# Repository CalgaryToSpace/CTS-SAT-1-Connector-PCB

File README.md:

# CTS-SAT-1-Connector-PCB
A PCB with SMD connector receptacles to find pin 1 more easily

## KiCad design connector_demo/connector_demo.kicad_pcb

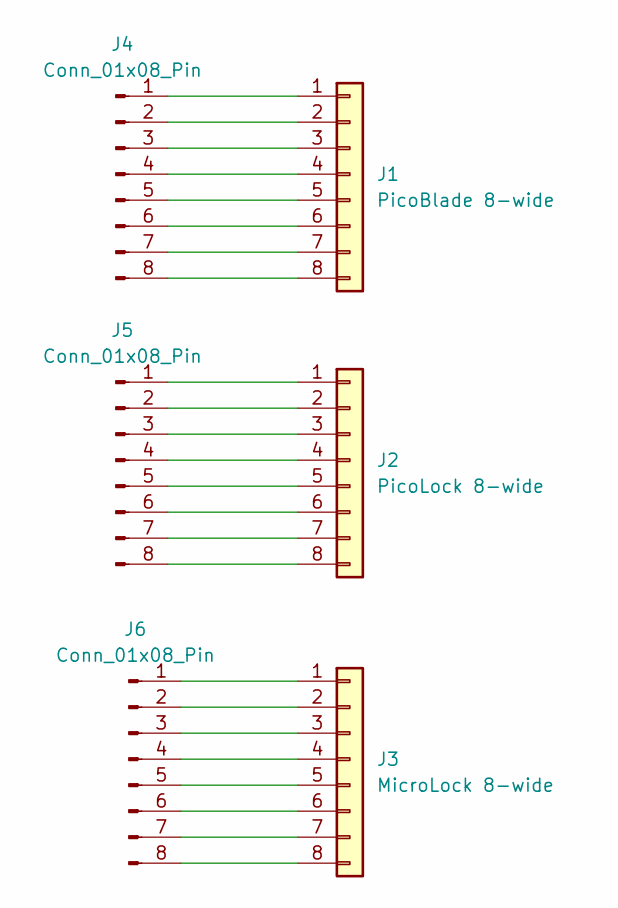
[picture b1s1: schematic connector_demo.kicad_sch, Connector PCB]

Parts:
J1: PicoBlade 8-wide; Molex_PicoBlade_53261-0871_1x08-1MP_P1.25mm_Horizontal
J2: PicoLock 8-wide; Molex_Pico-Lock_504050-0891_1x08-1MP_P1.50mm_Horizontal
J3: MicroLock 8-wide; CONN08_5055670871_MOL
J4, J5, J6: Conn_01x08_Pin; PinHeader_1x08_P2.54mm_Vertical

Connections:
unnamed: J1.1, J4.1
unnamed: J1.2, J4.2
unnamed: J1.3, J4.3
unnamed: J1.4, J4.4
unnamed: J1.5, J4.5
unnamed: J1.6, J4.6
unnamed: J1.7, J4.7
unnamed: J1.8, J4.8
unnamed: J2.1, J5.1
unnamed: J2.2, J5.2
unnamed: J2.3, J5.3
unnamed: J2.4, J5.4
unnamed: J2.5, J5.5
unnamed: J2.6, J5.6
unnamed: J2.7, J5.7
unnamed: J2.8, J5.8
unnamed: J3.1, J6.1
unnamed: J3.2, J6.2
unnamed: J3.3, J6.3
unnamed: J3.4, J6.4
unnamed: J3.5, J6.5
unnamed: J3.6, J6.6
unnamed: J3.7, J6.7
unnamed: J3.8, J6.8

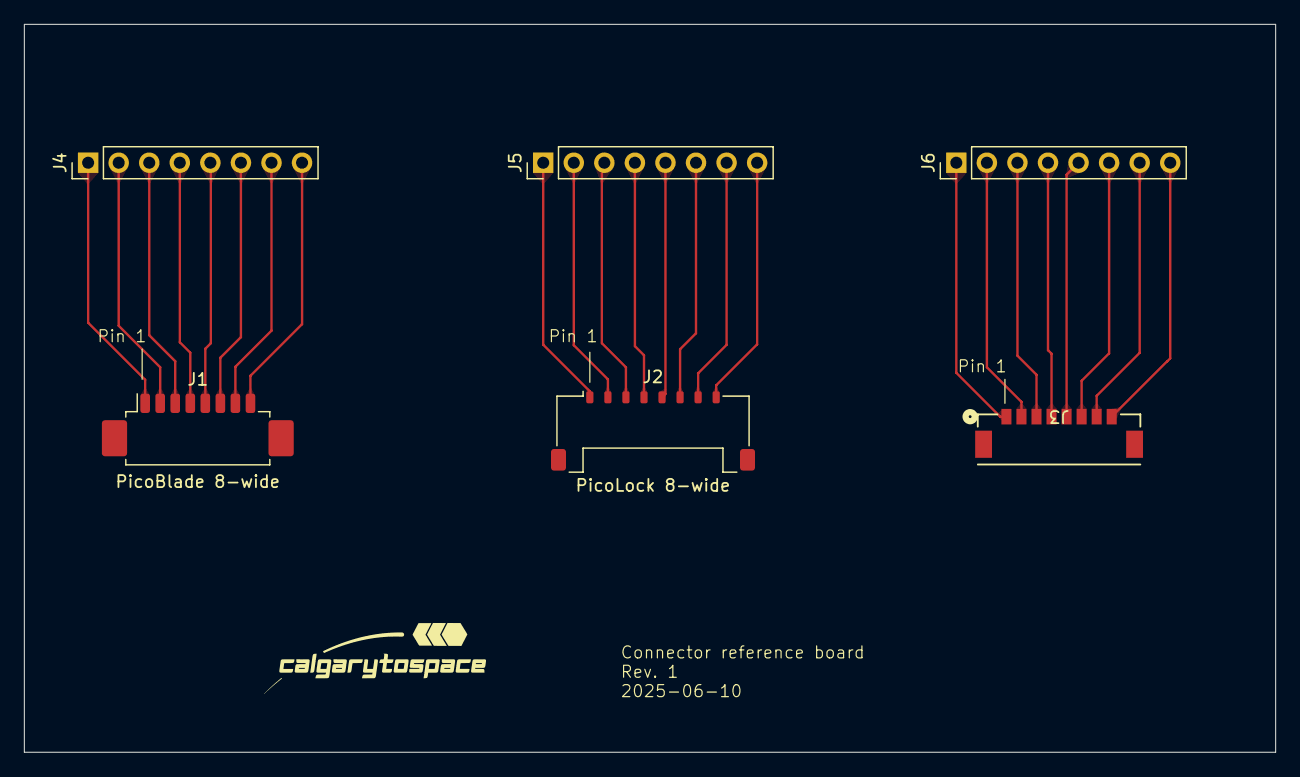
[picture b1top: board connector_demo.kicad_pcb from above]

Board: 2 copper layers, 104.0 x 60.5 mm, 6 parts (0 on the bottom side), 24 nets.

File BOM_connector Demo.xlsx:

Reference | Qty | Value | DNP | Exclude from BOM | Exclude from Board | Footprint | Datasheet
J1 | 1 | PicoBlade 8-wide |  |  |  | Connector_Molex:Molex_PicoBlade_53261-0871_1x08-1MP_P1.25mm_Horizontal | ~
J2 | 1 | PicoLock 8-wide |  |  |  | Connector_Molex:Molex_Pico-Lock_504050-0891_1x08-1MP_P1.50mm_Horizontal | ~
J3 | 1 | MicroLock 4-wide |  |  |  | microlock:CONN04_5055670471_MOL | ~
J4,J5 | 2 | Conn_01x08_Pin |  |  |  | Connector_PinHeader_2.54mm:PinHeader_1x08_P2.54mm_Vertical | ~
J6 | 1 | Conn_01x04_Pin |  |  |  | Connector_PinHeader_2.54mm:PinHeader_1x04_P2.54mm_Vertical | ~

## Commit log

2025-03-28 added pcb design files
2025-03-30 added connector names
    still confirming pin 1
2025-03-30 confirmed pin 1
2025-03-30 added header pins and traces
2025-03-30 Fixed microlock connector, generated BOM
2025-03-30 gerber
2025-03-30 removed gerber
2025-06-11 update microlock to 8 pin, confirmed pin 1
